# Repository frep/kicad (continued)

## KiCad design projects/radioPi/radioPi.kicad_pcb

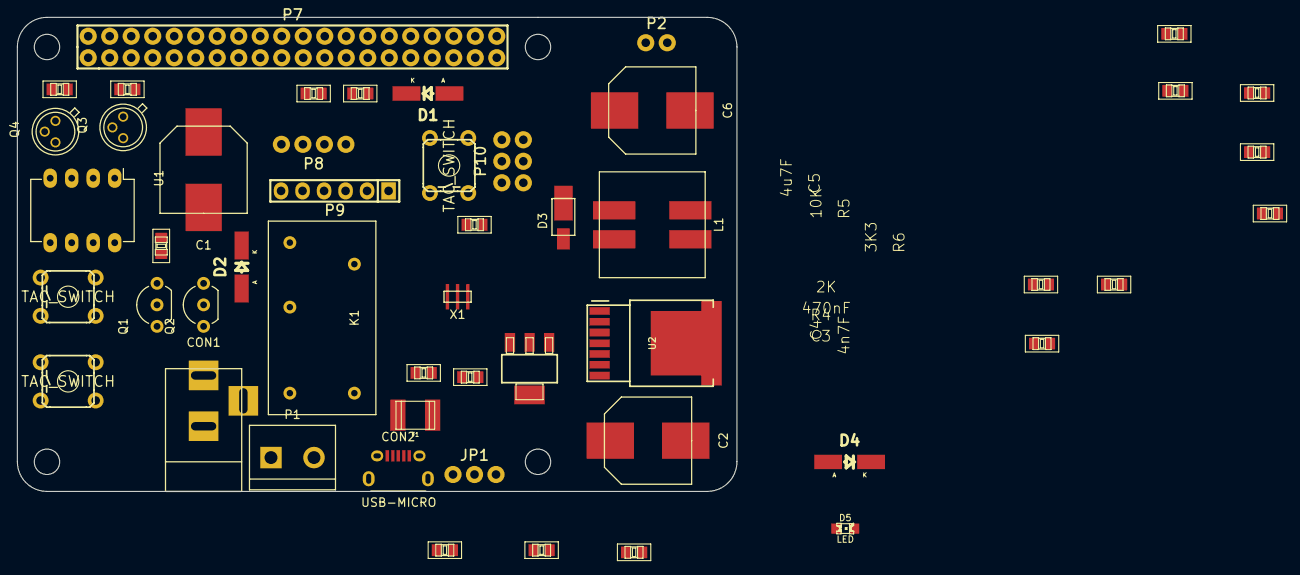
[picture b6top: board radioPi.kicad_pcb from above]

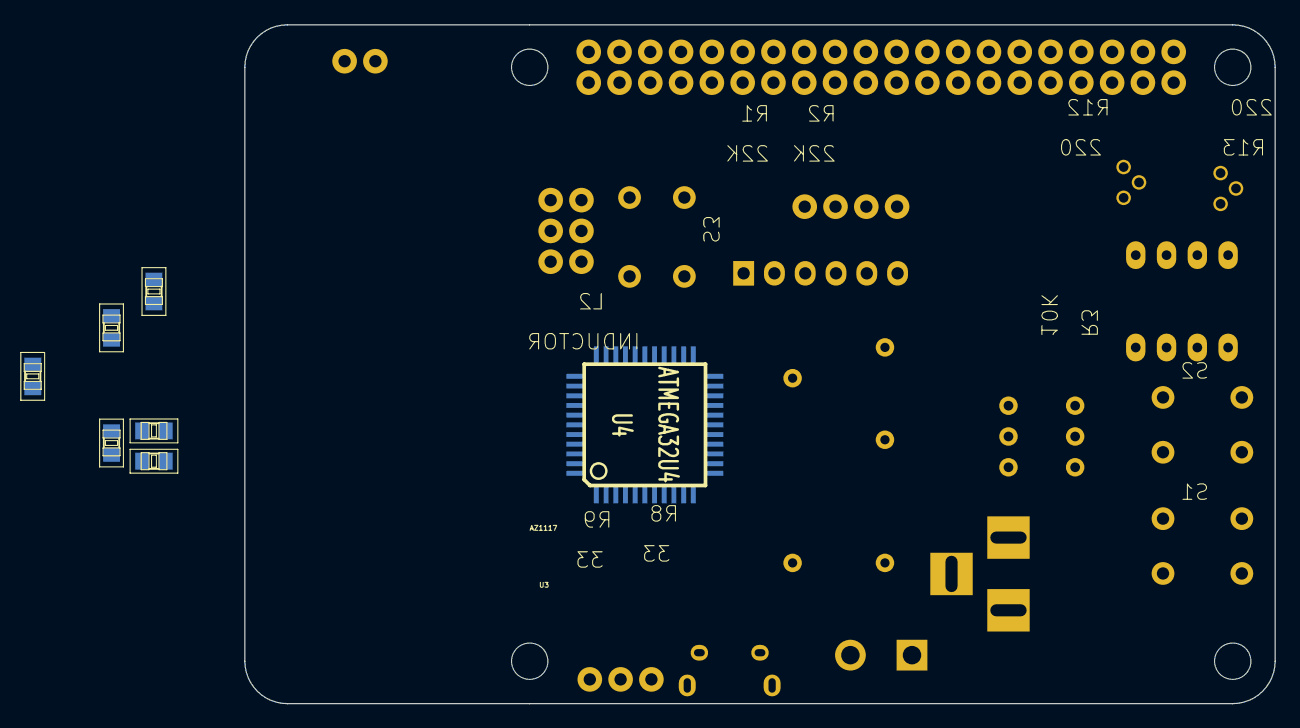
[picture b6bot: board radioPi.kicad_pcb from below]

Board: 2 copper layers, 85.0 x 56.0 mm, 61 parts (7 on the bottom side), 48 nets, no tracks yet.

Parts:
C1, C2, C6: 100uF; Cap_Nichicon
C3: 470nF; C0805
C4: 4n7F; C0805
C5, C10, C11: 4u7F; C0805
C7, C8, C9, C12: 100nF; C0805
C13: 1uF; C0805
CON1: BARREL_JACK
CON2: USB-MICRO; USB_Micro
D1, D2, D4: DIODE; Diode-MiniMELF_Handsoldering
D3: DIODESCH; DO-221BC
D5: LED; LED-0805
F1: FUSE; C1812
JP1: JUMPER3; Pin_Proto_Straight_1x03
K1: RELAY; Relay_SPDT
L1: InductorsCoupled
L2: INDUCTOR; R0805
P1: CONN_2; Terminal2
P2: CONN_2; Pin_Proto_Straight_1x02
P3, P4, P5, P6: CONN_1; MountingHole_3mm
P7: CONN_20X2; Pin_Proto_Straight_2x20
P8: CONN_4; Pin_Proto_Straight_1x04
P9: CONN_6; Pin_Header_Straight_1x06
P10: CONN_3X2; Pin_Proto_Straight_2x03
Q1, Q2: 2N3904; TO-92_Inline_Wide
Q3, Q4: 2N3904; TO-18_3Pin
R1, R2: 22K; R0805
R3, R5, R7, R10, R14: 10K; R0805
R4: 2K; R0805
R6: 3K3; R0805
R8, R9: 33; R0805
R11: 330; R0805
R12, R13: 220; R0805
S1, S2, S3: TAC_SWITCH; TACTILE-PTH
U1: OPTO_TRANSISTOR; DIP-8_W7.62mm
U2: LT1370
U3: AZ1117; SOT223
U4: ATMEGA32U4; TQFP44
X1: Resonator

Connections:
3V3: C7.1, C11.1, D4.2, L2.2, P8.3, P9.4, P10.2, R7.1, U3.2, U3.4, U4.2, U4.14, U4.24, U4.34
5V: C6.1, D3.2, JP1.3, P2.1, Q3.2, Q4.2, R5.2
/RPiAndArduino/shutdown: Q4.3, R13.2
/RPiAndArduino/startup: Q3.3, R12.2
A0: D1.1, P7.36, R14.1, U4.36
C1: C2.1, CON1.1, K1.2, L1.3, S2.3, S2.4, U1.7, U2.3, U2.7
C2: Q1.3, R3.1, S1.1, S1.2, U1.6
D5: R12.1, U4.31
D6: P8.2, U4.27
D9: P9.5, U4.29
D10: P9.2, U4.30
D11: P9.3, U4.12
D12: R13.1, U4.26
D+: R9.2, U4.4
D-: R8.2, U4.3
E1: D2.2, K1.3, K1.4, P1.1, S2.1, S2.2, U1.8
E2: C1.2, C2.2, C3.2, C4.2, C6.2, C8.2, C9.2, C10.2, C11.2, C12.2, C13.2, CON1.2, CON1.3, CON2.5, CON2.6, CON2.7, CON2.8, CON2.9, L1.4, P1.2, P2.2, P7.6, P7.9, P7.14, P7.20, P7.25, P7.30, P7.34, P7.39, P8.1, P8.4, P9.1, P9.6, P10.6, Q2.1, R6.1, R10.1, R11.1, R14.2, S1.3, S1.4, S3.1, S3.2, U1.2, U1.3, U1.5, U2.4, U2.8, U3.1, U4.5, U4.15, U4.23, U4.35, U4.43, X1.2
MISO: P10.1, U4.11
MOSI: P10.4, U4.10
unnamed: C1.1, R1.1, R2.1, R3.2
unnamed: C3.1, R4.1
unnamed: C4.1, R4.2, U2.1
unnamed: C5.1, L1.1, U2.5
unnamed: C5.2, D3.1, L1.2
unnamed: C8.1, U4.6
unnamed: C9.1, C10.1, JP1.2, U3.3
unnamed: C12.1, U4.42
unnamed: C13.1, L2.1, U4.44
unnamed: CON2.1, F1.1
unnamed: CON2.2, R8.1
unnamed: CON2.3, R9.1
unnamed: D1.2, R1.2
unnamed: D2.1, K1.5, Q1.2, Q2.2
unnamed: D5.1, U4.32
unnamed: D5.2, R11.2
unnamed: K1.1, R2.2
unnamed: Q1.1, Q2.3
unnamed: Q3.1, U1.1
unnamed: Q4.1, U1.4
unnamed: R5.1, R6.2, U2.2
unnamed: R10.2, U4.33
unnamed: U4.16, X1.3
unnamed: U4.17, X1.1
RESET: C7.2, D4.1, P10.5, R7.2, S3.3, S3.4, U4.13
SCK: P10.3, U4.9
SCL: P7.5, U4.18
SDA: P7.3, U4.19
VBUS: F1.2, JP1.1, U4.7

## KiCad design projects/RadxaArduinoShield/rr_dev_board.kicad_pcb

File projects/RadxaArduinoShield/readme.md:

Radxa Arduino Shield
====================
description is following soon...

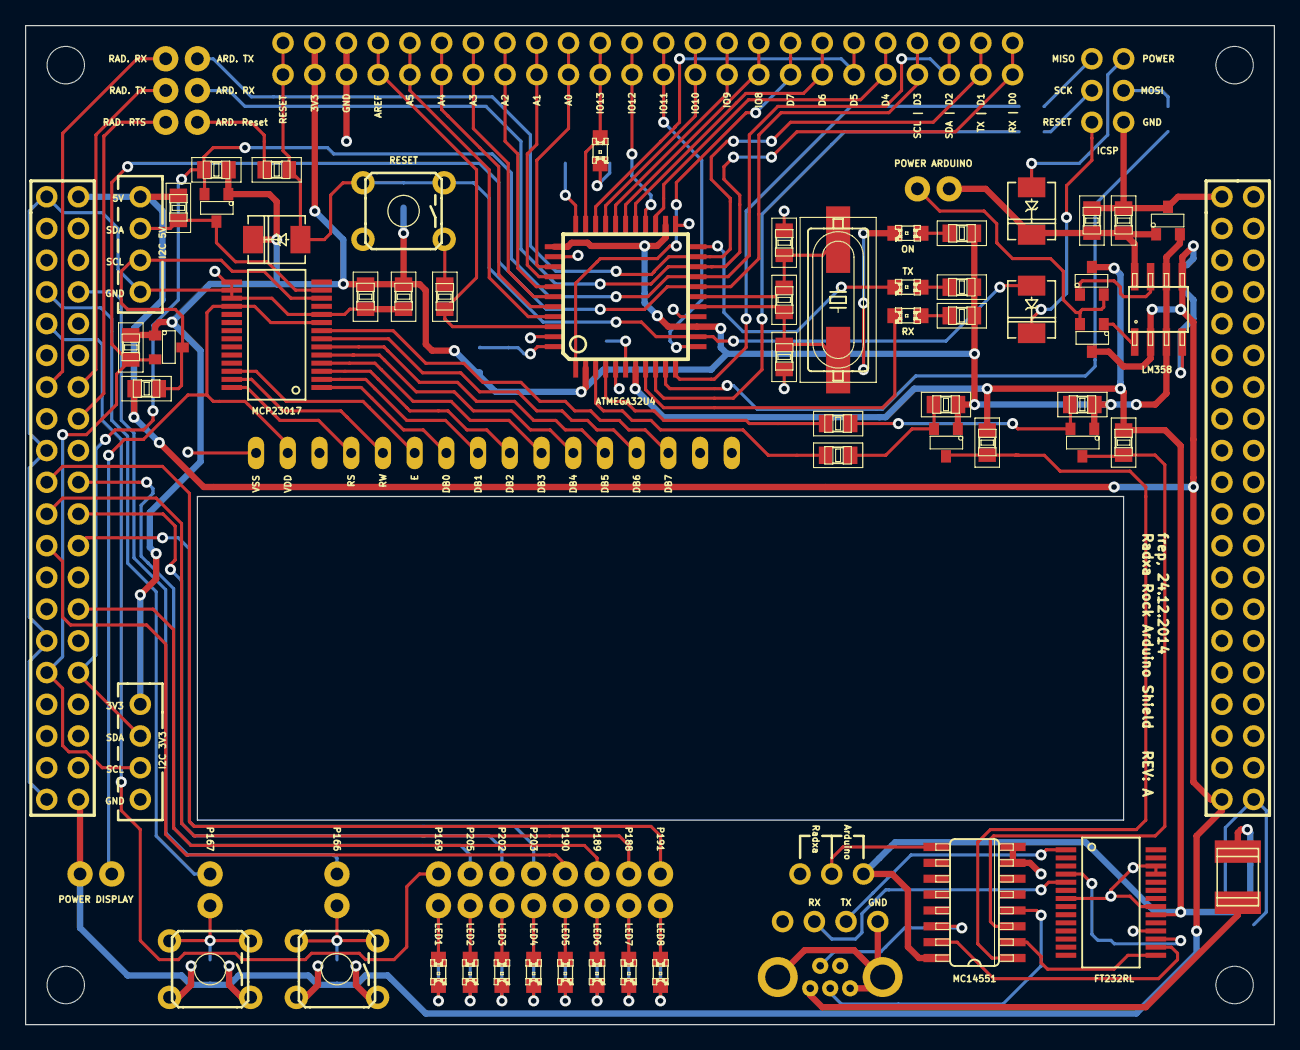
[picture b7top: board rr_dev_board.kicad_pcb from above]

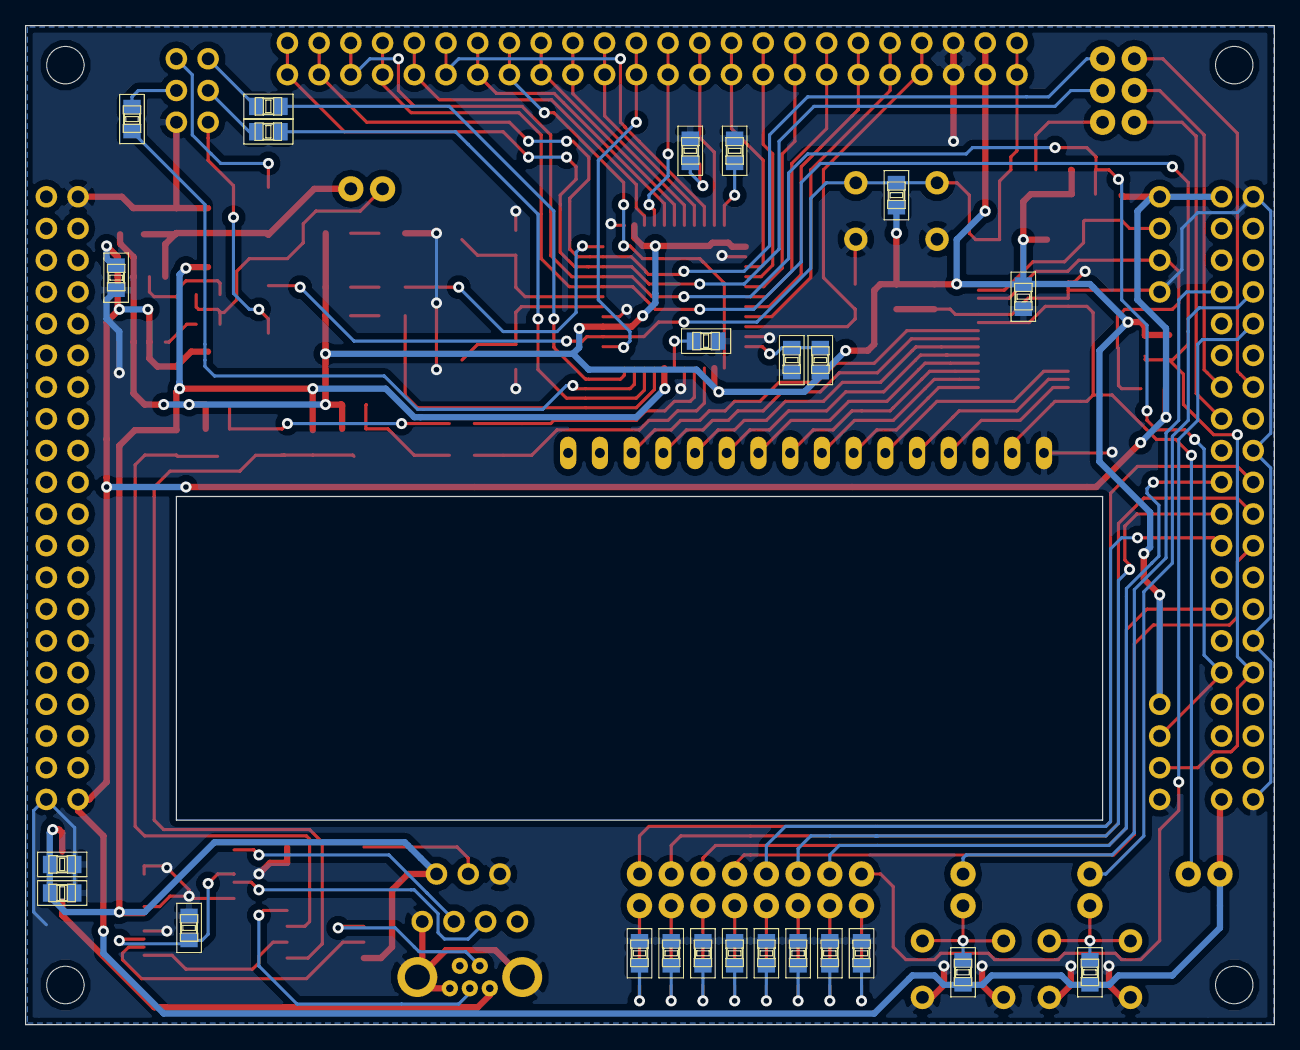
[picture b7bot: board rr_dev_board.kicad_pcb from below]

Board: 2 copper layers, 100.0 x 80.0 mm, 108 parts (24 on the bottom side), 110 nets.

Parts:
C1, C3, C5, C7, C8, C9, C13, C14: 100nF; C0805
C2: 4.7uF; C0805
C4, C6: 18pF; C0805
C10, C11, C12: 1uF; C0805
CON1: USB-MINI-B-Vert; Vertical_USB_Mini_B
D1, D2, D3, D4, D5, D6, D7, D8: LED; LED-0805
D9, D10, D11: DIODE; DO-214AC
D12: RX; LED-0805
D13: TX; LED-0805
D14: Pin13; LED-0805
D15: ON; LED-0805
F1: FUSE; C1812
IC1: OPAMP-DUALU; SOIC8
JP1, JP2, JP3, JP4, JP5, JP6, JP7, JP8, JP9, JP10, JP11, JP12, JP14, JP15, JP16: JUMPER; Pin_Proto_Straight_1x02
JP13: JUMPER3; Pin_Proto_Straight_1x03
L1: Ferrit Bead; R0805
P1, P6: CONN_20X2; Pin_Proto_Header_Straight_2x20
P2, P3, P4, P5: CONN_1; MountingHole_3mm
P7, P11, P12: CONN_4; Pin_Proto_Straight_1x04
P8, P9: CONN_24; Pin_Proto_Straight_1x24
P10: CONN_3X2; Pin_Proto_Straight_2x03
Q1, Q2, Q5, Q6: MOSFET-N; SOT23
Q3, Q4: MOSFET-P; SOT23
R1, R2, R11, R12, R13, R14, R15, R26, R30, R31, R32, R33: 10K; R0805
R3, R4, R5, R6, R7, R8, R9, R10: 100; R0805
R16, R19: 1M; R0805
R17, R18: 33; R0805
R20, R21, R22: 4K7; R0805
R23, R24, R25, R27: 1K; R0805
S1, S2, S3: TAC_SWITCH; TACTILE-PTH
U1: MC14551; SO16
U2: FT232RL; SSOP28
U3: ATMEGA32U4; TQFP44
U4: AP7333; SOT23
U5: MCP23017; SSOP28
X1: 16MHz; HC49UP
X2: OLED-1602; LCD1602_NoSilkScreen

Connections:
+5VD: IC1.2, IC1.5, JP15.1, P1.2, P1.40, P6.39, P11.4, Q3.3, R1.1, R2.1, R19.1, R30.1, R31.1
/USB2Serial/ARD_D+: Q1.2, R12.2, R18.2
/USB2Serial/ARD_D-: Q2.2, R14.2, R17.2
/USB2Serial/RADXA_RX: P7.3, U2.5
/USB2Serial/RADXA_TX: P7.2, U2.1
/arduino/ARD_Reset: C14.1, JP16.2
A0: P8.10, P9.10, U3.36
A1: P8.9, P9.9, U3.37
A2: P8.8, P9.8, U3.38
A3: P8.7, P9.7, U3.39
A4: P8.6, P9.6, U3.40
A5: P8.5, P9.5, U3.41
AREF: C9.1, P8.4, P9.4, U3.42
D0/RX: JP1.2, P8.24, P9.24, U3.20
D1/TX: JP2.1, P8.23, P9.23, U3.21
D2/SDA: P1.32, P8.22, P9.22, P12.2, Q5.2, R32.2, U3.19
D3/SCL: P1.31, P8.21, P9.21, P12.3, Q6.2, R33.2, U3.18
D4: P8.20, P9.20, U3.25
D5: P8.19, P9.19, U3.31
D6: P8.18, P9.18, U3.27
D7: P8.17, P9.17, U3.1
D_E: U5.26, X2.6
D_RS: U5.28, X2.4
D_RW: U5.27, X2.5
GND: C1.2, C2.2, C3.2, C4.2, C5.2, C6.2, C7.2, C8.2, C9.2, C10.2, C11.2, C12.2, C13.2, CON1.5, CON1.6, CON1.7, D15.2, IC1.4, JP13.1, P1.1, P1.17, P1.29, P1.39, P6.1, P6.29, P6.40, P7.1, P8.3, P9.3, P10.6, P11.1, P12.4, R3.2, R4.2, R5.2, R6.2, R7.2, R8.2, R9.2, R10.2, R19.2, R25.2, R26.2, S1.1, S1.2, S2.1, S2.2, S3.1, S3.2, U1.7, U1.8, U2.7, U2.18, U2.21, U2.25, U2.26, U3.5, U3.15, U3.23, U3.35, U3.43, U4.3, U5.10, U5.15, U5.16, U5.17, X2.1
GPIO166: JP4.2, P1.8
GPIO_167: JP3.2, P1.7
GPIO_169: JP5.1, P1.9
HWB: R26.1, U3.33
IO_8: P8.16, P9.16, U3.28
IO_9: P8.15, P9.15, U3.29
IO_10: P8.14, P9.14, U3.30
IO_11: P8.13, P9.13, U3.12
IO_12: P8.12, P9.12, U3.26
IO_13: D14.1, P8.11, P9.11, U3.32
MISO: R20.1, U3.11
MOSI: R22.1, U3.10
unnamed: C3.1, U2.4, U2.17
unnamed: C4.1, R16.1, U3.16, X1.1
unnamed: C6.1, R16.2, U3.17, X1.2
unnamed: C8.1, U3.6
unnamed: C10.1, L1.1, U3.44
unnamed: CON1.1, F1.1
unnamed: CON1.2, U1.14
unnamed: CON1.3, U1.4
unnamed: D1.1, JP5.2
unnamed: D1.2, R3.1
unnamed: D2.1, JP6.2
unnamed: D2.2, R4.1
unnamed: D3.1, JP7.2
unnamed: D3.2, R5.1
unnamed: D4.1, JP8.2
unnamed: D4.2, R6.1
unnamed: D5.1, JP9.2
unnamed: D5.2, R7.1
unnamed: D6.1, JP10.2
unnamed: D6.2, R8.1
unnamed: D7.1, JP11.2
unnamed: D7.2, R9.1
unnamed: D8.1, JP12.2
unnamed: D8.2, R10.1
unnamed: D10.2, P10.5
unnamed: D11.1, P10.2
unnamed: D12.1, R23.1
unnamed: D13.1, R24.1
unnamed: D14.2, R25.1
unnamed: D15.1, R27.2
unnamed: IC1.1, Q3.1
unnamed: IC1.7, Q4.1
unnamed: JP3.1, R1.2, S1.3, S1.4
unnamed: JP4.1, R2.2, S2.3, S2.4
unnamed: JP13.2, U1.9
unnamed: JP14.1, Q3.2, Q4.2
unnamed: JP15.2, U5.9, U5.18, X2.2
unnamed: P10.1, R20.2
unnamed: P10.3, R21.1
unnamed: P10.4, R22.2
unnamed: Q1.3, R11.2, U1.3
unnamed: Q2.3, R13.2, U1.1
unnamed: R17.1, U3.3
unnamed: R18.1, U3.4
unnamed: U1.2, U2.15
unnamed: U1.15, U2.16
unnamed: U5.1, X2.7
unnamed: U5.2, X2.8
unnamed: U5.3, X2.9
unnamed: U5.4, X2.10
unnamed: U5.5, X2.11
unnamed: U5.6, X2.12
unnamed: U5.7, X2.13
unnamed: U5.8, X2.14
REG_Vin: C11.1, C13.1, D11.2, IC1.8, JP14.2, U4.1
RESET: C14.2, D9.1, D10.1, P8.1, P9.1, R15.2, S3.3, S3.4, U3.13
RXLED: D12.2, U3.8
SCK: R21.2, U3.9
SCL_5V: P11.2, Q6.3, R31.2, U5.12
SDA_5V: P11.3, Q5.3, R30.2, U5.13
SPI1_CLK: JP9.1, P1.23
SPI1_CSN0: JP12.1, P1.19
SPI1_RX: JP11.1, P1.21
SPI1_TX: JP10.1, P1.28
TXLED: D13.2, U3.22
UART0_RTS: JP16.1, P1.16
UART0_RX: JP2.2, P1.13
UART0_TX: JP1.1, P1.14
UART3_RTSN: JP6.1, P1.20
UART3_RX: JP7.1, P1.22
UART3_TX: JP8.1, P1.24
USB_5V: C1.1, C2.1, F1.2, JP13.3, Q4.3, R11.1, R13.1, U1.16, U2.20, U3.7
VCC_3V3: C5.1, C7.1, C12.1, D9.2, IC1.3, IC1.6, L1.2, P8.2, P9.2, P12.1, Q1.1, Q2.1, Q5.1, Q6.1, R12.1, R14.1, R15.1, R23.2, R24.2, R27.1, R32.1, R33.1, U3.2, U3.14, U3.24, U3.34, U4.2

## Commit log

2014-10-22 library and readme added
2014-10-26 library updated
2014-10-26 mosfet updated
2014-10-27 ToDo's added
2014-10-27 library updated, backup-files deleted
2014-10-27 part description started
2014-10-27 update library
2014-11-04 lm358 added
2014-11-04 footprint library added
2014-11-05 more footprints added
2014-11-28 C0805 added
2014-11-30 more parts added
2014-12-12 update readme.md with some usefull links
2014-12-24 project structure added
2014-12-24 markdown typo
2014-12-25 adding project files
2014-12-25 readme's updated
2014-12-25 gerber files added
2014-12-25 zipped gerber-files for ordering
2014-12-26 new part USB_A_Conn_stacked
2014-12-26 project files added
2014-12-29 LabBenchPsu update
2014-12-29 LabBenchPsu updated
2015-01-12 update LabBenchPsu
2015-05-31 start ArduinoController project
2015-05-31 remove unused file
2015-06-01 working on schematics of Arduino Controller
2015-06-02 work in progress
2015-06-05 schematic passes ERC
2015-06-05 pdf updated
2015-06-07 started with new footprints
2015-06-09 working on footprints and netlist
2015-06-12 footprints done
2015-06-15 small changes
2015-06-15 new project PowerBox added
2015-06-16 update PowerBox
2015-06-17 powerbox updated
2015-06-21 automatic poweroff with LBO signal
2015-06-21 update schematic
2015-06-24 new display driver with 74HC595
2015-06-25 new footprints added
2015-06-26 attiny replaced with arduino leonardo clone
2015-06-27 small modifications
2015-06-27 erc warnings solved
2015-06-28 protection parts added
2015-07-02 Switches changed
2015-07-02 part informations added
2015-07-02 netlist finished
2015-07-02 pcb layout started
2015-07-03 basic part placement
2015-07-03 routing started
2015-07-05 layout in progress
2015-07-05 pcb layout in progress
2015-07-06 pcb layout still in progress
2015-07-07 pcb layout most traces done
2015-07-07 traces done
2015-07-07 pcb still not finished
2015-07-08 start changing power lines
2015-07-09 arduino pins labled
2015-07-10 frep logo added
2015-07-10 digikey partnumbers in schematic added
2015-07-11 ruby script for bom.xml processing added
2015-07-12 pdfs for some layers generated
2015-07-12 BOM added
2015-07-13 Small changes in bom2csv.rb
2015-07-13 instructions for silkscreen pictures added
2015-07-13 usb connectors moved to bottom side
2015-07-13 try to fix .csv
2015-07-13 use comma as separator
2015-07-14 value in csv added
2015-07-14 csv new generated
2015-07-18 footprints changed and tracks adjusted
2015-07-23 ina219 footprint and pin-assignement changed
2015-07-23 new footprint routed
2015-07-23 missing trace routed
2015-07-24 schematic updated
2015-07-24 working on silk screen texts
2015-07-25 board size adjustment in progress
2015-07-31 board size adjusted
2015-07-31 forgot to save
2015-07-31 gerber files created
2015-08-02 3d part workflow descriped
2015-08-03 started with 3d parts
2015-08-04 2d sketch in progress
2015-08-05 exploring 123d design
2015-08-06 getting used to 123d
2015-08-07 3d part in progress
2015-08-07 edges rounded
2015-08-10 stl exported
2015-08-30 3d part still had uncommited changes
2015-08-30 prepare new revision
2015-09-01 lt1370 added
2015-09-03 sepic schematic first draw
2015-09-04 schematic finished
2015-09-04 working on sepic
2015-09-05 still working on sepic
2015-09-05 layout started
2016-01-12 Sepic Rev A finished
2016-01-13 Updating gerber instructions
2016-01-19 new project
2016-01-19 working on EspDevBoard
2016-01-21 work on EspDevBoard
2016-01-23 EDB schematic done
2016-01-23 update pdf
2016-01-23 netlist created
2016-01-24 changing esp-12
2016-01-30 new footprint
2016-01-30 work on footprints and netlist
2016-01-31 start with pcb
2016-02-28 schematic changed
2016-03-02 Sepic updated
2016-03-05 finish EspDevBoard Rev. A
2016-03-12 testsoftware added
2016-04-25 sw changes
2016-07-06 work on labBenchPsu
2016-07-07 working on schematic and footprints
2016-07-09 work on pcb
2016-07-10 pcb in progress
2016-07-20 protective diodes added
2016-07-21 working on pcb
2016-07-23 initial routing done
2016-07-24 mounting holes moved
2016-08-17 finish frontpanel
2016-09-17 pdf schematic updated
2016-09-17 closing project
2016-09-17 start with labPsu
2016-09-18 readme added
2016-09-18 working on schematic
2016-09-18 redraw schematic
2016-10-01 constant current load added
2016-10-10 schematic more or less done
2016-11-02 schematic reviewed
2016-11-06 schematic with new DAC
2016-11-06 i2c addresses added
2016-11-06 sepic calculations added
